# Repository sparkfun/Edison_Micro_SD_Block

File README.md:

SparkFun Edison microSD Block
============================

[*SparkFun Edison microSD Block(DEV-13041)*](https://www.sparkfun.com/products/13041)

The microSD Block equips your Edioson with mass storage capability, so you can use it for data-logging or other related projects.

Repository Contents
-------------------
* **/Hardware** - All Eagle Design files (.brd, .sch)
* **/Production** -Test bed files and production panel files

License Information
-------------------

The hardware is released under [Creative Commons ShareAlike 4.0 International](https://creativecommons.org/licenses/by-sa/4.0/).
The code is beerware; if you see me (or any other SparkFun employee) at the local, and you've found our code helpful, please buy us a round!

Distributed as-is; no warranty is given.

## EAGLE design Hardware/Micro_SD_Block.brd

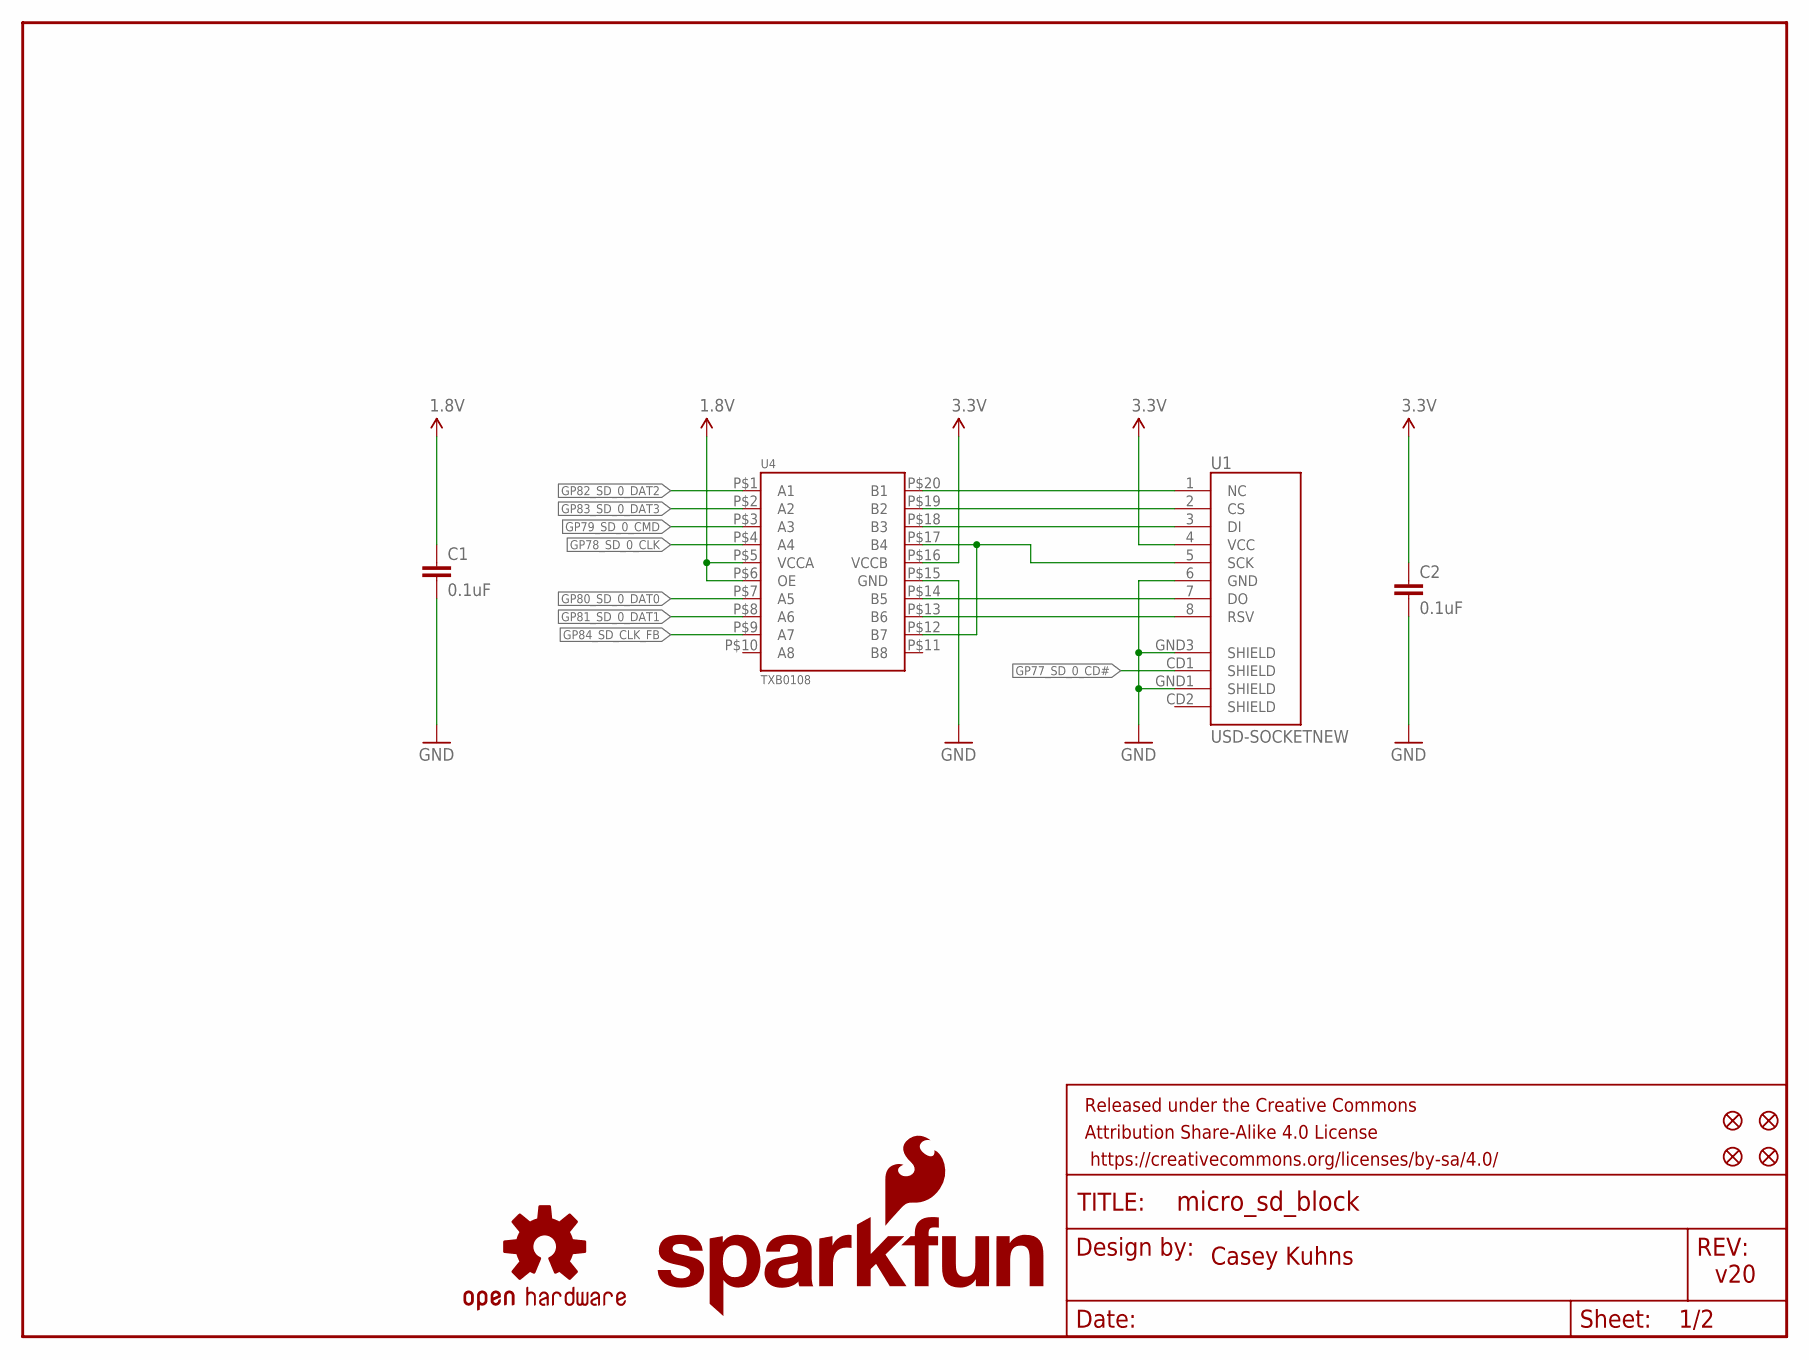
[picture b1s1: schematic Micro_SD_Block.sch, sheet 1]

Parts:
C1, C2: 0.1uF; 0603-CAP
FID1, FID2, FID3, FID4: FIDUCIAL1X2; FIDUCIAL-1X2
FRAME1: FRAME-LETTER; CREATIVE_COMMONS
LOGO1: OSHW-LOGOS; OSHW-LOGO-S
LOGO4: SFE_LOGO_NAME_FLAME.1_INCH; SFE_LOGO_NAME_FLAME_.1
U1: USD-SOCKETNEW; MICRO-SD-SOCKET-PP
U4: TXB0108; UFDFN-20

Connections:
1.8V: C1.1, U4.P$5 (VCCA), U4.P$6 (OE); also elsewhere on the board
3.3V: C2.1, U1.4 (VCC), U4.P$16 (VCCB); also elsewhere on the board
GND: C1.2, C2.2, U1.6 (GND), U1.GND1 (SHIELD), U1.GND3 (SHIELD), U4.P$15 (GND); also elsewhere on the board
GP77_SD_0_CD#: U1.CD1 (SHIELD); also elsewhere on the board
GP78_SD_0_CLK: U4.P$4 (A4); also elsewhere on the board
GP79_SD_0_CMD: U4.P$3 (A3); also elsewhere on the board
GP80_SD_0_DAT0: U4.P$7 (A5); also elsewhere on the board
GP81_SD_0_DAT1: U4.P$8 (A6); also elsewhere on the board
GP82_SD_0_DAT2: U4.P$1 (A1); also elsewhere on the board
GP83_SD_0_DAT3: U4.P$2 (A2); also elsewhere on the board
GP84_SD_CLK_FB: U4.P$9 (A7); also elsewhere on the board
unnamed: U1.1 (NC), U4.P$20 (B1)
unnamed: U1.2 (CS), U4.P$19 (B2)
unnamed: U1.3 (DI), U4.P$18 (B3)
unnamed: U1.7 (DO), U4.P$14 (B5)
unnamed: U1.8 (RSV), U4.P$13 (B6)
SCK: U1.5 (SCK), U4.P$12 (B7), U4.P$17 (B4)

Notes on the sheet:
Casey Kuhns
v20

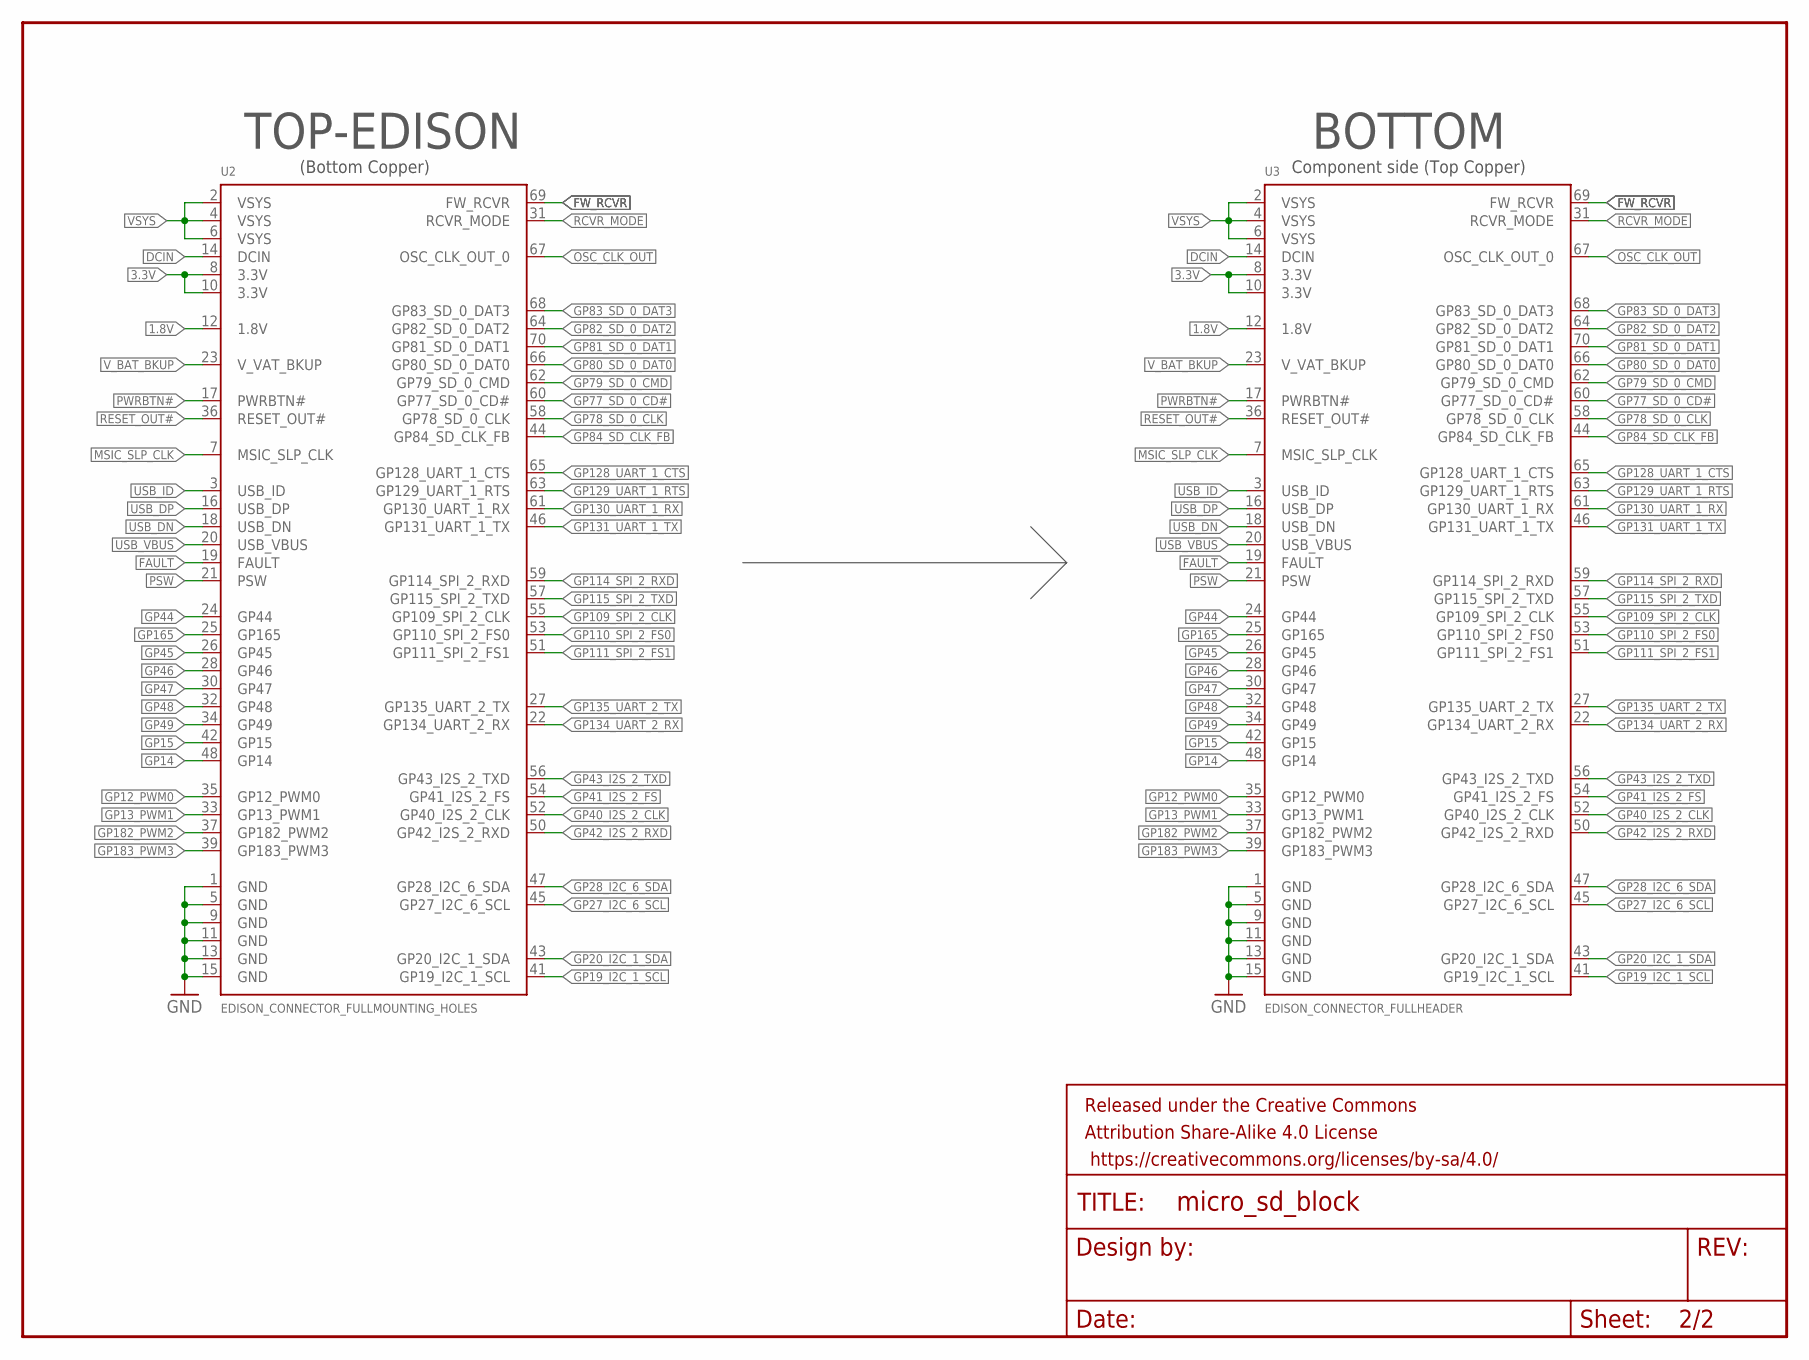
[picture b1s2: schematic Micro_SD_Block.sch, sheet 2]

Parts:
FRAME2: FRAME-LETTER; CREATIVE_COMMONS
U2: EDISON_CONNECTOR_FULLMOUNTING_HOLES; EDISON_DAUGHTER
U3: EDISON_CONNECTOR_FULLHEADER; DF40C-70DP-0.4(51)

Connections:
1.8V: U2.12 (1.8V), U3.12 (1.8V); also elsewhere on the board
3.3V: U2.8 (3.3V), U2.10 (3.3V), U3.8 (3.3V), U3.10 (3.3V); also elsewhere on the board
DCIN: U2.14 (DCIN), U3.14 (DCIN)
FAULT: U2.19 (FAULT), U3.19 (FAULT)
FW_RCVR: U2.69 (FW_RCVR), U3.69 (FW_RCVR)
GND: U2.1 (GND), U2.5 (GND), U2.9 (GND), U2.11 (GND), U2.13 (GND), U2.15 (GND), U3.1 (GND), U3.5 (GND), U3.9 (GND), U3.11 (GND), U3.13 (GND), U3.15 (GND); also elsewhere on the board
GP12_PWM0: U2.35 (GP12_PWM0), U3.35 (GP12_PWM0)
GP13_PWM1: U2.33 (GP13_PWM1), U3.33 (GP13_PWM1)
GP14: U2.48 (GP14), U3.48 (GP14)
GP15: U2.42 (GP15), U3.42 (GP15)
GP19_I2C_1_SCL: U2.41 (GP19_I2C_1_SCL), U3.41 (GP19_I2C_1_SCL)
GP20_I2C_1_SDA: U2.43 (GP20_I2C_1_SDA), U3.43 (GP20_I2C_1_SDA)
GP27_I2C_6_SCL: U2.45 (GP27_I2C_6_SCL), U3.45 (GP27_I2C_6_SCL)
GP28_I2C_6_SDA: U2.47 (GP28_I2C_6_SDA), U3.47 (GP28_I2C_6_SDA)
GP40_I2S_2_CLK: U2.52 (GP40_I2S_2_CLK), U3.52 (GP40_I2S_2_CLK)
GP41_I2S_2_FS: U2.54 (GP41_I2S_2_FS), U3.54 (GP41_I2S_2_FS)
GP42_I2S_2_RXD: U2.50 (GP42_I2S_2_RXD), U3.50 (GP42_I2S_2_RXD)
GP43_I2S_2_TXD: U2.56 (GP43_I2S_2_TXD), U3.56 (GP43_I2S_2_TXD)
GP44: U2.24 (GP44), U3.24 (GP44)
GP45: U2.26 (GP45), U3.26 (GP45)
GP46: U2.28 (GP46), U3.28 (GP46)
GP47: U2.30 (GP47), U3.30 (GP47)
GP48: U2.32 (GP48), U3.32 (GP48)
GP49: U2.34 (GP49), U3.34 (GP49)
GP77_SD_0_CD#: U2.60 (GP77_SD_0_CD#), U3.60 (GP77_SD_0_CD#); also elsewhere on the board
GP78_SD_0_CLK: U2.58 (GP78_SD_0_CLK), U3.58 (GP78_SD_0_CLK); also elsewhere on the board
GP79_SD_0_CMD: U2.62 (GP79_SD_0_CMD), U3.62 (GP79_SD_0_CMD); also elsewhere on the board
GP80_SD_0_DAT0: U2.66 (GP80_SD_0_DAT0), U3.66 (GP80_SD_0_DAT0); also elsewhere on the board
GP81_SD_0_DAT1: U2.70 (GP81_SD_0_DAT1), U3.70 (GP81_SD_0_DAT1); also elsewhere on the board
GP82_SD_0_DAT2: U2.64 (GP82_SD_0_DAT2), U3.64 (GP82_SD_0_DAT2); also elsewhere on the board
GP83_SD_0_DAT3: U2.68 (GP83_SD_0_DAT3), U3.68 (GP83_SD_0_DAT3); also elsewhere on the board
GP84_SD_CLK_FB: U2.44 (GP84_SD_CLK_FB), U3.44 (GP84_SD_CLK_FB); also elsewhere on the board
GP109_SPI_2_CLK: U2.55 (GP109_SPI_2_CLK), U3.55 (GP109_SPI_2_CLK)
GP110_SPI_2_FS0: U2.53 (GP110_SPI_2_FS0), U3.53 (GP110_SPI_2_FS0)
GP111_SPI_2_FS1: U2.51 (GP111_SPI_2_FS1), U3.51 (GP111_SPI_2_FS1)
GP114_SPI_2_RXD: U2.59 (GP114_SPI_2_RXD), U3.59 (GP114_SPI_2_RXD)
GP115_SPI_2_TXD: U2.57 (GP115_SPI_2_TXD), U3.57 (GP115_SPI_2_TXD)
GP128_UART_1_CTS: U2.65 (GP128_UART_1_CTS), U3.65 (GP128_UART_1_CTS)
GP129_UART_1_RTS: U2.63 (GP129_UART_1_RTS), U3.63 (GP129_UART_1_RTS)
GP130_UART_1_RX: U2.61 (GP130_UART_1_RX), U3.61 (GP130_UART_1_RX)
GP131_UART_1_TX: U2.46 (GP131_UART_1_TX), U3.46 (GP131_UART_1_TX)
GP134_UART_2_RX: U2.22 (GP134_UART_2_RX), U3.22 (GP134_UART_2_RX)
GP135_UART_2_TX: U2.27 (GP135_UART_2_TX), U3.27 (GP135_UART_2_TX)
GP165: U2.25 (GP165), U3.25 (GP165)
GP182_PWM2: U2.37 (GP182_PWM2), U3.37 (GP182_PWM2)
GP183_PWM3: U2.39 (GP183_PWM3), U3.39 (GP183_PWM3)
MSIC_SLP_CLK: U2.7 (MSIC_SLP_CLK), U3.7 (MSIC_SLP_CLK)
OSC_CLK_OUT: U2.67 (OSC_CLK_OUT_0), U3.67 (OSC_CLK_OUT_0)
PSW: U2.21 (PSW), U3.21 (PSW)
PWRBTN#: U2.17 (PWRBTN#), U3.17 (PWRBTN#)
RCVR_MODE: U2.31 (RCVR_MODE), U3.31 (RCVR_MODE)
RESET_OUT#: U2.36 (RESET_OUT#), U3.36 (RESET_OUT#)
USB_DN: U2.18 (USB_DN), U3.18 (USB_DN)
USB_DP: U2.16 (USB_DP), U3.16 (USB_DP)
USB_ID: U2.3 (USB_ID), U3.3 (USB_ID)
USB_VBUS: U2.20 (USB_VBUS), U3.20 (USB_VBUS)
VSYS: U2.2 (VSYS), U2.4 (VSYS), U2.6 (VSYS), U3.2 (VSYS), U3.4 (VSYS), U3.6 (VSYS)
V_BAT_BKUP: U2.23 (V_VAT_BKUP), U3.23 (V_VAT_BKUP)

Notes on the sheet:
TOP-EDISON
BOTTOM
Component side (Top Copper)
(Bottom Copper)

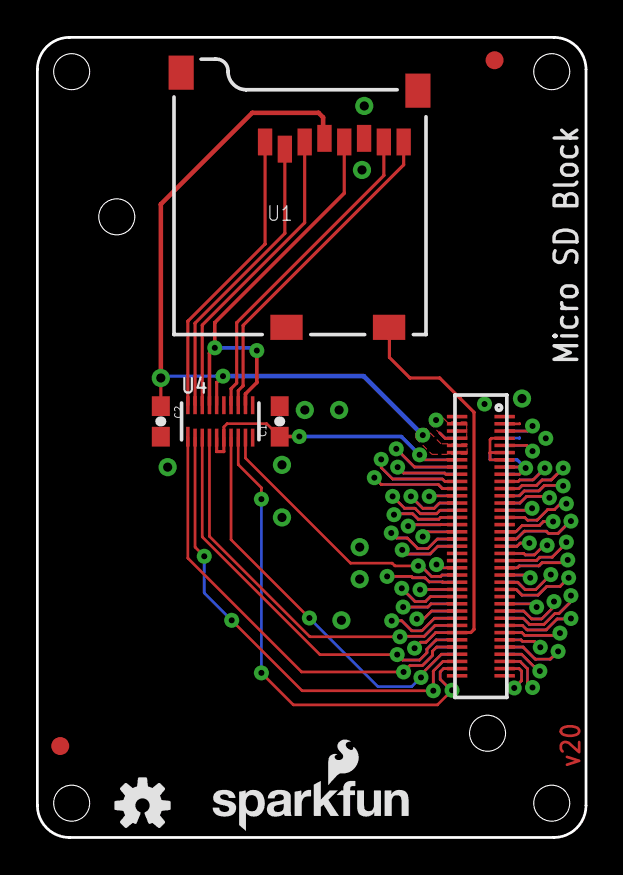
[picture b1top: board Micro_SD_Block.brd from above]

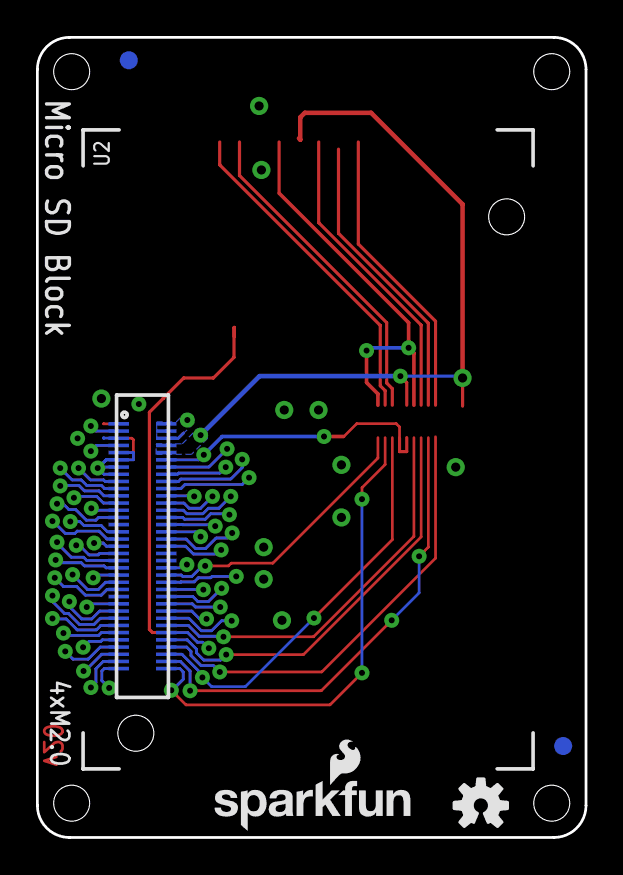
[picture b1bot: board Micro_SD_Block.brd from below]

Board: 2 copper layers, 30.5 x 44.5 mm, 16 parts (6 on the bottom side), 64 nets.

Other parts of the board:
LOGO2: OSHW-LOGOS; OSHW-LOGO-S
LOGO3: SFE_LOGO_NAME_FLAME.1_INCH; SFE_LOGO_NAME_FLAME_.1

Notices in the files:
parts and their libraries:
SparkFun-Aesthetics: Licensing: Creative Commons ShareAlike 4.0 International - https://creativecommons.org/licenses/by-sa/4.0
SparkFun-Aesthetics: Released under the Creative Commons Attribution Share-Alike 4.0 License
SparkFun-Aesthetics: Released under the Creative Commons
